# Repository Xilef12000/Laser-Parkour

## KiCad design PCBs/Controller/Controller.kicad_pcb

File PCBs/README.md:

# Library sources:
## RPi Pico
from [github.com/ncarandini/KiCad-RP-Pico](https://github.com/ncarandini/KiCad-RP-Pico):
- `MCU_RaspberryPi_and_Boards.kicad_sym`
- `Pico.wrl`
- `RPi_Pico_SMD_TH.kicad_mod` 

## Würth Elektronik
converted from files provided by [Würth Elektronik](https://www.we-online.com/):
- `WR-DC DC Power Jack Right Angled (6.4).kicad_mod`
- `WR-MJ Modular Jack Horizontal Shielded w. EMI Panel Finger 8P8C Tab Up.kicad_mod`
- `WS-ENTV_4820XX514001.kicad_mod`

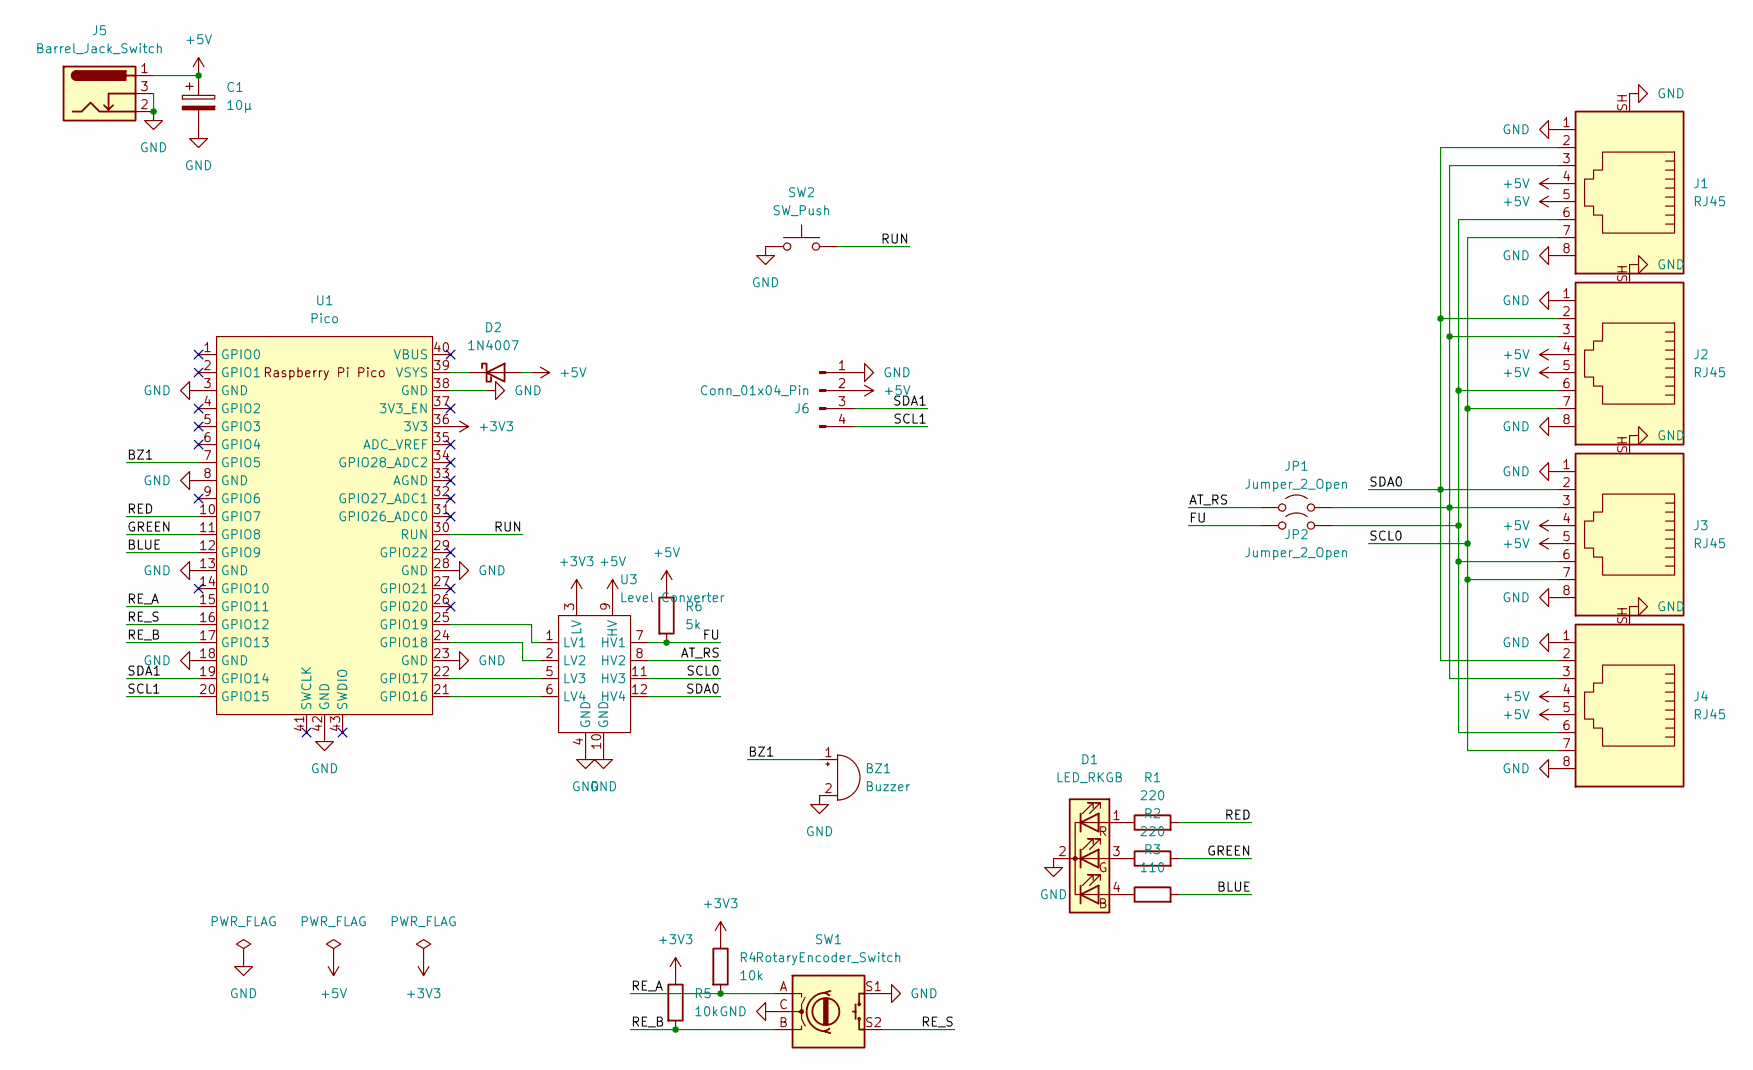
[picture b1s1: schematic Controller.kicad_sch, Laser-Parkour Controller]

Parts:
BZ1: Buzzer; Buzzer_12x9.5RM7.6
C1: 10μ; CP_Radial_D5.0mm_P2.00mm
D1: LED_RKGB; LED_D5.0mm-4_RGB_Wide_Pins
D2: 1N4007; D_DO-41_SOD81_P7.62mm_Horizontal
J1, J2, J3, J4: RJ45; WR-MJ Modular Jack Horizontal Shielded w. EMI Panel Finger 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
J5: Barrel_Jack_Switch; WR-DC DC Power Jack Right Angled (6.4)
J6: Conn_01x04_Pin; PinHeader_1x04_P2.54mm_Vertical
JP1, JP2: Jumper_2_Open; SolderJumper-2_P1.3mm_Open_RoundedPad1.0x1.5mm
R1, R2: 220; R_Axial_DIN0207_L6.3mm_D2.5mm_P10.16mm_Horizontal
R3: 110; R_Axial_DIN0207_L6.3mm_D2.5mm_P10.16mm_Horizontal
R4, R5: 10k; R_Axial_DIN0207_L6.3mm_D2.5mm_P10.16mm_Horizontal
R6: 5k; R_Axial_DIN0207_L6.3mm_D2.5mm_P10.16mm_Horizontal
SW1: RotaryEncoder_Switch; WS-ENTV_4820XX514001
SW2: SW_Push; SW_PUSH_6mm_H4.3mm
U1: Pico; RPi_Pico_SMD_TH
U3: Level Converter; Level_Converter

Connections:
+3V3: R4.1, R5.1, U1.36 (3V3), U3.3 (LV)
+5V: C1.1, D2.2 (A), J1.4, J1.5, J2.4, J2.5, J3.4, J3.5, J4.4, J4.5, J5.1, J6.2, R6.1, U3.9 (HV)
/AT_RS: JP1.1 (A), U3.8 (HV2)
/BLUE: R3.2, U1.12 (GPIO9)
/BZ1: BZ1.1 (+), U1.7 (GPIO5)
/FU: JP2.1 (A), R6.2, U3.7 (HV1)
/GREEN: R2.2, U1.11 (GPIO8)
/RED: R1.2, U1.10 (GPIO7)
/RE_A: R4.2, SW1.A, U1.15 (GPIO11)
/RE_B: R5.2, SW1.B, U1.17 (GPIO13)
/RE_S: SW1.S2, U1.16 (GPIO12)
/RUN: SW2.2, U1.30 (RUN)
/SCL0: J1.7, J2.7, J3.7, J4.7, U3.11 (HV3)
/SCL1: J6.4, U1.20 (GPIO15)
/SDA0: J1.2, J2.2, J3.2, J4.2, U3.12 (HV4)
/SDA1: J6.3, U1.19 (GPIO14)
GND: BZ1.2 (-), C1.2, D1.2 (K), J1.1, J1.8, J1.SH, J2.1, J2.8, J2.SH, J3.1, J3.8, J3.SH, J4.1, J4.8, J4.SH, J5.2, J5.3, J6.1, SW1.C, SW1.S1, SW2.1, U1.3 (GND), U1.8 (GND), U1.13 (GND), U1.18 (GND), U1.23 (GND), U1.28 (GND), U1.38 (GND), U1.42 (GND), U3.4 (GND), U3.10 (GND)
unnamed: D1.4 (BA), R3.1
unnamed: D1.3 (GA), R2.1
unnamed: D1.1 (RA), R1.1
unnamed: D2.1 (K), U1.39 (VSYS)
unnamed: J1.3, J2.3, J3.3, J4.3, JP1.2 (B)
unnamed: J1.6, J2.6, J3.6, J4.6, JP2.2 (B)
unnamed: U1.21 (GPIO16), U3.6 (LV4)
unnamed: U1.22 (GPIO17), U3.5 (LV3)
unnamed: U1.24 (GPIO18), U3.2 (LV2)
unnamed: U1.25 (GPIO19), U3.1 (LV1)

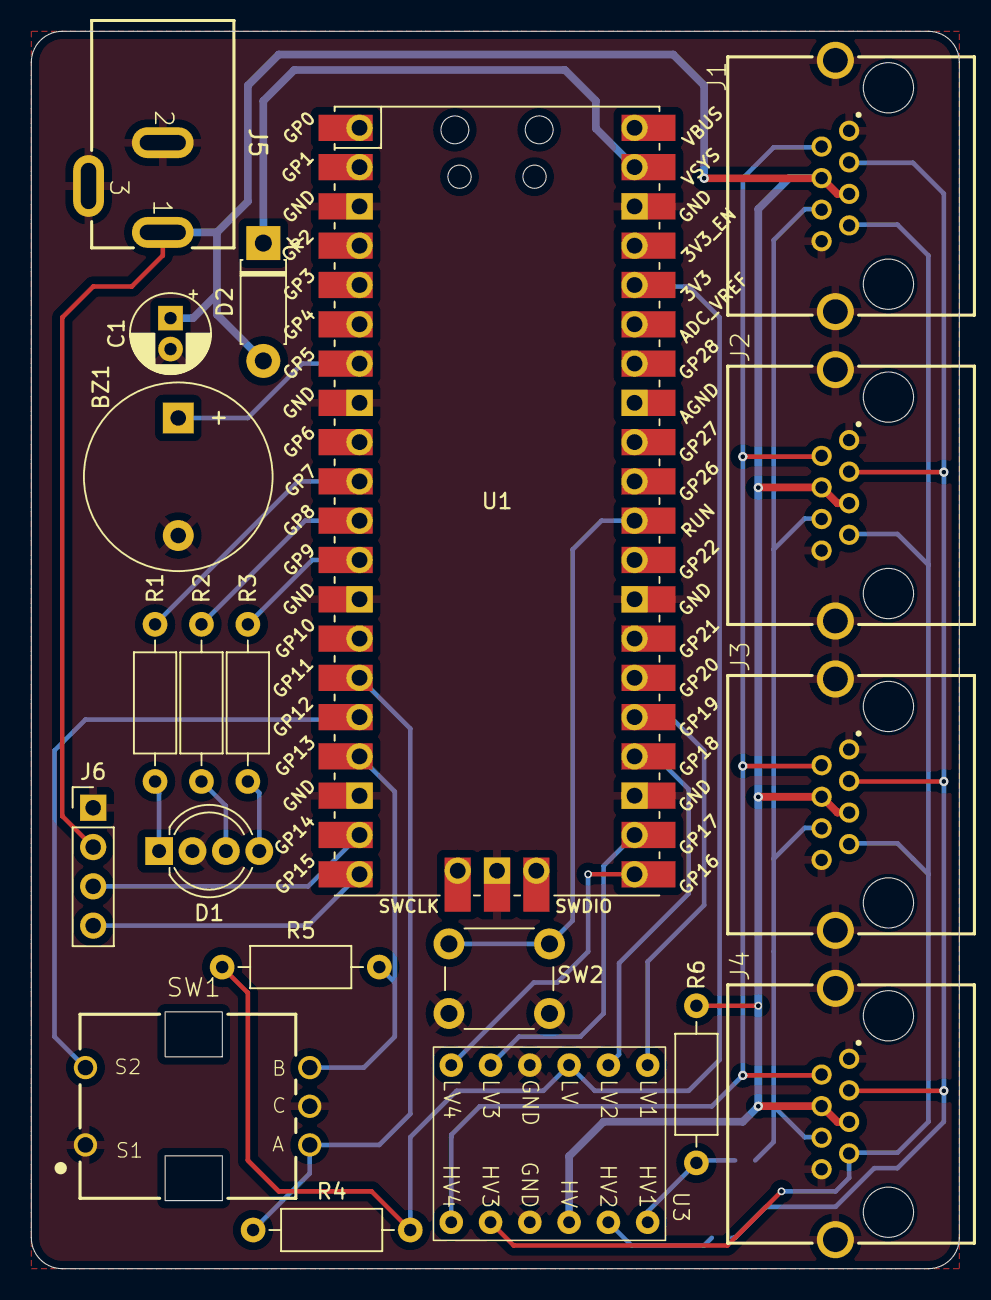
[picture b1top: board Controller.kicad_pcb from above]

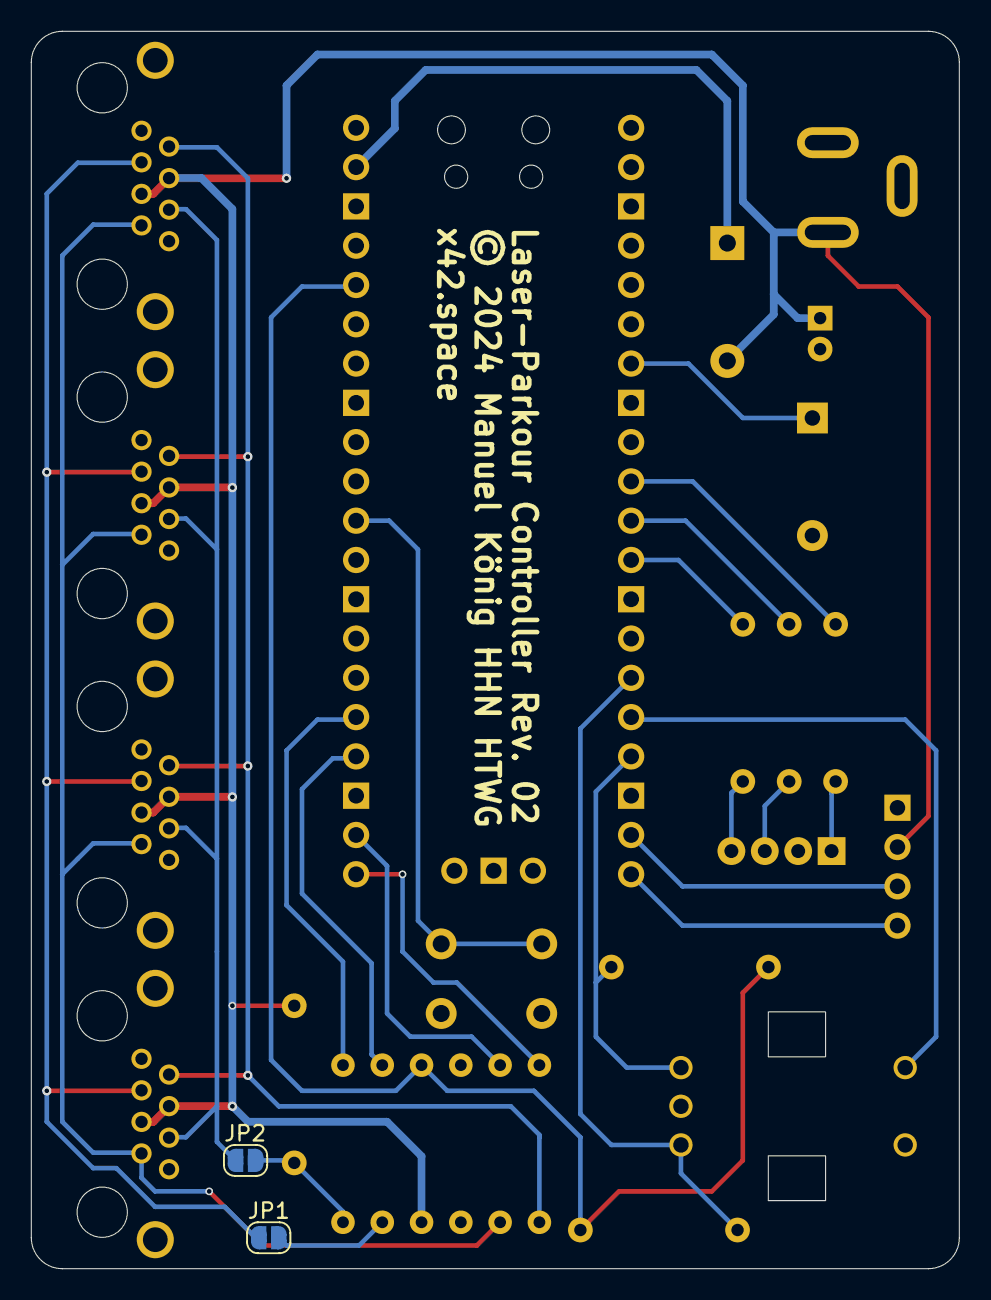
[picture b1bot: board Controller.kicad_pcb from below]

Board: 2 copper layers, 60.0 x 80.0 mm, 22 parts (2 on the bottom side), 27 nets.

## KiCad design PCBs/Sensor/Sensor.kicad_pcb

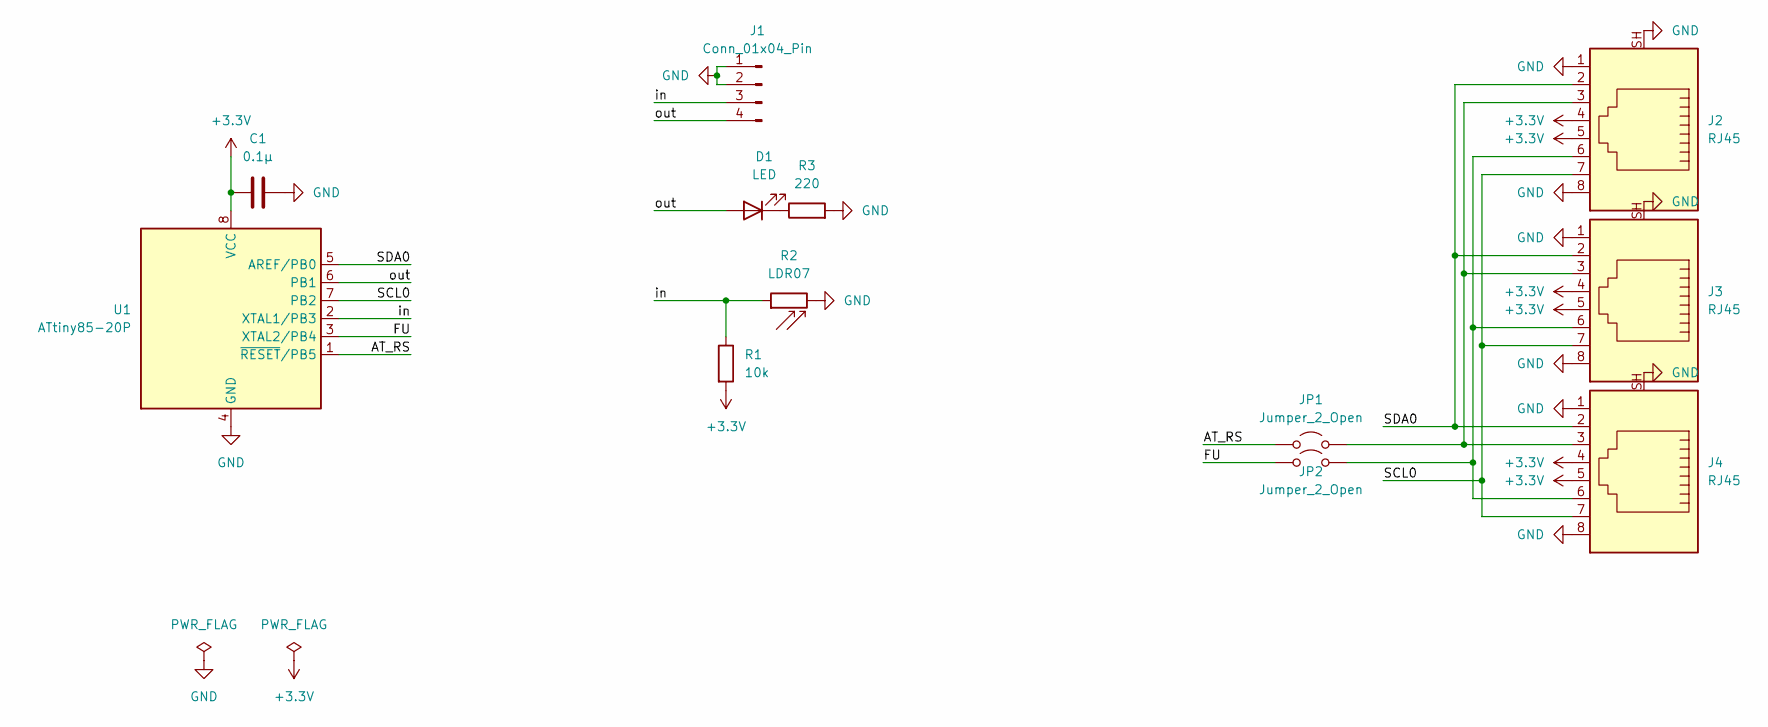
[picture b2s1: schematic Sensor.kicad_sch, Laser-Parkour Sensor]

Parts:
C1: 0.1μ; C_Disc_D3.0mm_W1.6mm_P2.50mm
D1: LED; LED_D5.0mm
J1: Conn_01x04_Pin; PinHeader_1x04_P2.54mm_Vertical
J2, J3, J4: RJ45; WR-MJ Modular Jack Horizontal Shielded w. EMI Panel Finger 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
JP1, JP2: Jumper_2_Open; SolderJumper-2_P1.3mm_Open_RoundedPad1.0x1.5mm
R1: 10k; R_Axial_DIN0207_L6.3mm_D2.5mm_P10.16mm_Horizontal
R2: LDR07; R_LDR_5.1x4.3mm_P3.4mm_Vertical
R3: 220; R_Axial_DIN0207_L6.3mm_D2.5mm_P10.16mm_Horizontal
U1: ATtiny85-20P; DIP-8_W7.62mm

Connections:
+3.3V: C1.1, J2.4, J2.5, J3.4, J3.5, J4.4, J4.5, R1.2, U1.8 (VCC)
/AT_RS: JP1.1 (A), U1.1 (~RESET/PB5)
/FU: JP2.1 (A), U1.3 (XTAL2/PB4)
/SCL0: J2.7, J3.7, J4.7, U1.7 (PB2)
/SDA0: J2.2, J3.2, J4.2, U1.5 (AREF/PB0)
/in: J1.3, R1.1, R2.1, U1.2 (XTAL1/PB3)
/out: D1.2 (A), J1.4, U1.6 (PB1)
GND: C1.2, J1.1, J1.2, J2.1, J2.8, J2.SH, J3.1, J3.8, J3.SH, J4.1, J4.8, J4.SH, R2.2, R3.2, U1.4 (GND)
unnamed: D1.1 (K), R3.1
unnamed: J2.3, J3.3, J4.3, JP1.2 (B)
unnamed: J2.6, J3.6, J4.6, JP2.2 (B)

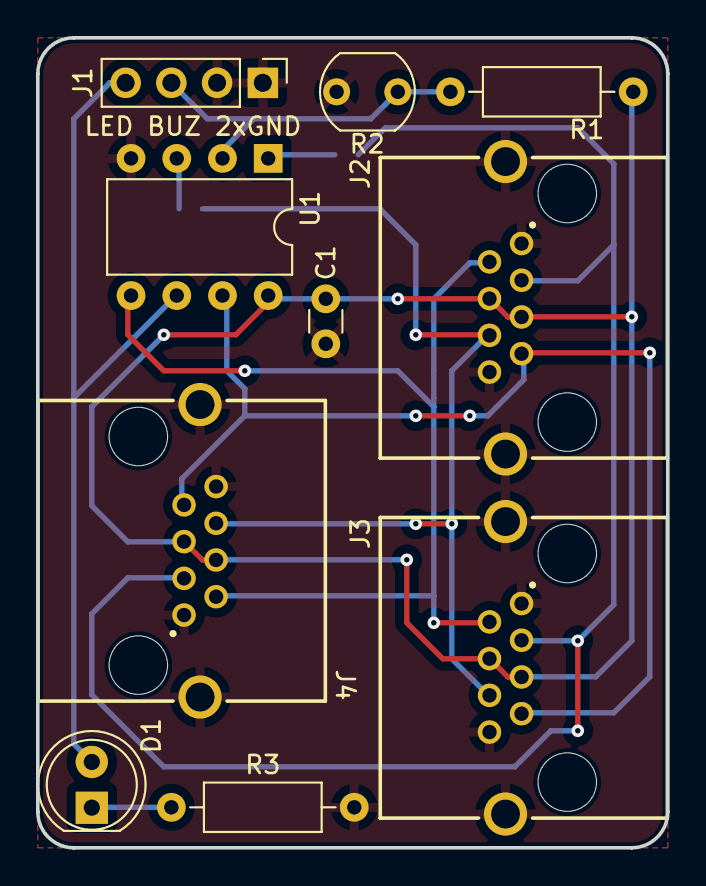
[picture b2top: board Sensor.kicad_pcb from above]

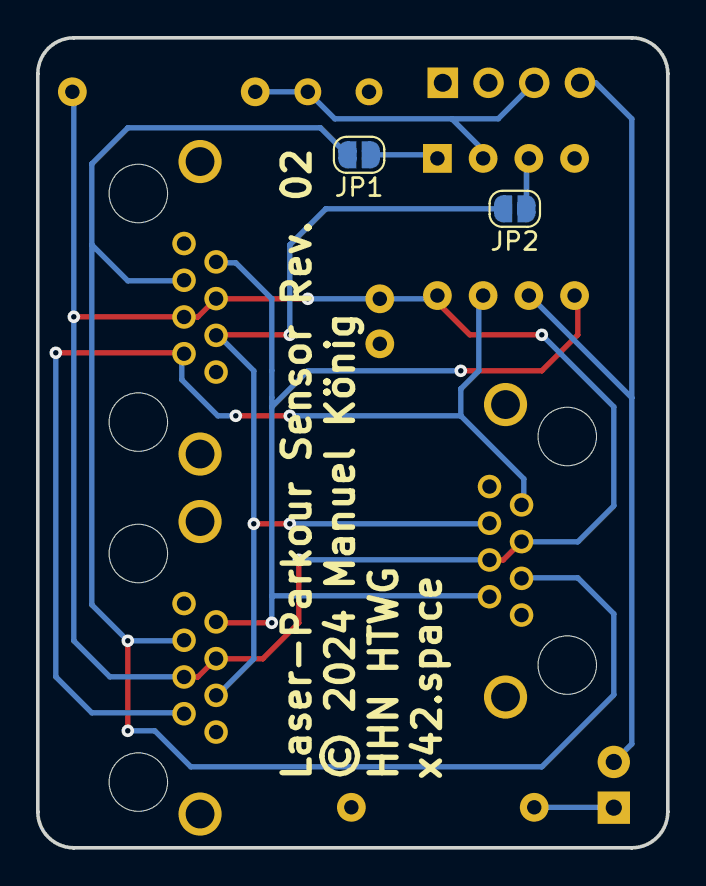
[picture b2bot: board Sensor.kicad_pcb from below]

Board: 2 copper layers, 35.0 x 45.0 mm, 12 parts (2 on the bottom side), 11 nets.

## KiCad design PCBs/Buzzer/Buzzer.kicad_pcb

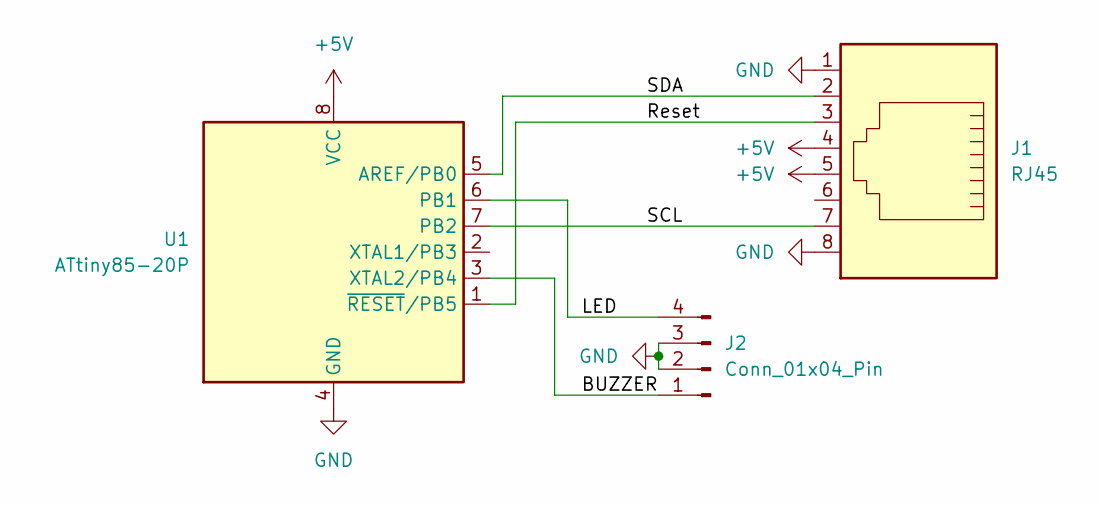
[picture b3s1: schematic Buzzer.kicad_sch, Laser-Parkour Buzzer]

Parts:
J1: RJ45; WR-MJ Modular Jack Horizontal Shielded w. EMI Panel Finger 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
J2: Conn_01x04_Pin; PinHeader_1x04_P2.54mm_Vertical
U1: ATtiny85-20P; DIP-8_W7.62mm

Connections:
+5V: J1.4, J1.5, U1.8 (VCC)
/BUZZER: J2.1, U1.3 (XTAL2/PB4)
/LED: J2.4, U1.6 (PB1)
/Reset: J1.3, U1.1 (~RESET/PB5)
/SCL: J1.7, U1.7 (PB2)
/SDA: J1.2, U1.5 (AREF/PB0)
GND: J1.1, J1.8, J1.S1, J1.S2, J2.2, J2.3, U1.4 (GND)

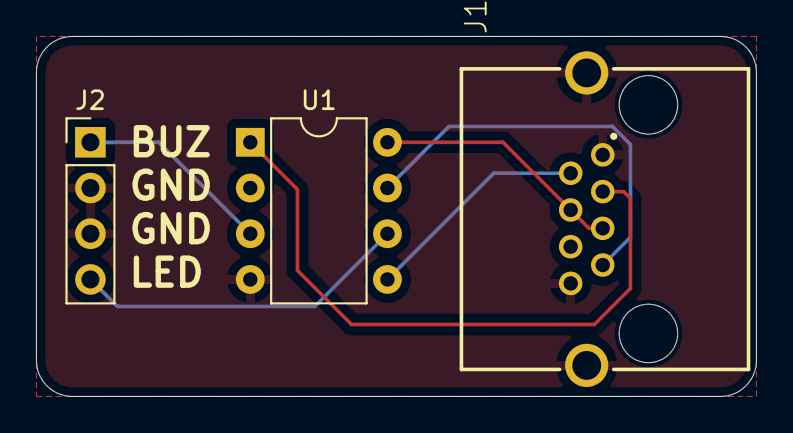
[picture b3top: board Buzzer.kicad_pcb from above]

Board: 2 copper layers, 40.0 x 20.0 mm, 3 parts (0 on the bottom side), 7 nets.

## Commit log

2021-06-18 current laser parcour program
2021-06-18 README
2021-06-18 test sketch
2021-06-18 delet old Readme
2021-06-18 new README.md
2021-06-18 extended wiring diagram
2021-06-18 update wiring diagram
2021-06-18 update dev
2021-06-19 update wiring diagram
    update wiring diagram and rename from "extended wiring diagram" to "wiring diagram 3.0"
2021-06-20 updaate
2021-06-20 add laserdiods
2021-06-20 add laser diode
2021-06-20 now with custom laser-diods
2021-07-23 update wiring diagramm
2021-08-01 corrections for release
2021-08-01 changes for release
2021-08-01 added programs
2021-08-08 correcting "parcour" to "parkour"
2021-08-08 new version 2.1.2
2021-08-08 correcting more spelling mistakes
2021-08-08 corrected spelling mistakes
2021-08-08 changed "laserlab" to "laser-parkour"
2021-08-08 changes.
2021-08-08 deleted arduino stuff
2021-08-08 changed version in comment
2021-08-08 changes for parallel photo-diodes
2021-08-11 deleted unnecessary notes
2021-08-11 deleting old .h-files
2021-08-11 class stuff
2021-08-11 fixing a few things for release
2021-08-11 fixing
2021-08-11 also fixing
2021-08-11 deleted laser-diode image stuff
2021-10-04 added useful stuff
2021-10-05 complete new script
2021-10-05 new wiring diagram
2021-10-11 added a class and functions
2021-10-12 new complicated stuff
2021-10-22 webinterface
2021-10-22 added the testsketch
2021-10-22 name input
2021-10-24 renamed sketch to sketch_esp
2021-10-24 added vs code stuff
2021-10-24 more vs-code stuff
2021-10-24 worked with %appdata%
2021-10-25 web interface working
2021-10-25 removed Serial.println
2021-10-25 new stuff
2021-10-26 working on web-interface
2021-10-28 bug fix
    Fixed the bug, that the sketch loops when laser gets interrupted, and in this time doesn't recognise, when the finish-button gets pressed
2021-10-28 updated the README and added the README.html file
2021-10-28 updated the README
2021-10-28 working web-interface
2021-10-28 better i-frame
2021-10-31 preparing for sd-card
2021-11-01 moved webpage, .htm instead of .html
2021-11-01 new wiring diagramm
2021-11-01 web-page changes
2021-11-01 read from sd-card
2021-11-01 corrected the web-interface
2021-11-01 updated the wiring diagramm
2021-11-01 renamed table files
2021-11-01 .htmll to .htm
2021-11-01 VS-Code stuff
2021-11-26 added 3D-files
2021-11-29 renamed 3d-file folder
2022-01-17 added the Batteriehalter 3d-files
2022-04-01 Laserstrahlung image as svg
2022-04-07 transparent background
2022-04-07 added Laser-Symbol
    original source: https://upload.wikimedia.org/wikipedia/commons/archive/9/94/20080912112604%21Laser-symbol.svg
2022-04-08 new photos
2024-08-18 simple I2C communication
2024-08-18 Sensor PCB schematic
2024-08-24 assigned footprints
2024-08-24 routing
2024-08-24 added info text
2024-08-24 Buzzer
2024-08-24 update footprint
2024-08-24 added nc
2024-08-25 added library content
2024-08-25 controller
2024-08-25 pcb page setup
2024-09-01 update RJ45 pins and pwr_flag
2024-09-01 integrate buzzer PCB into Sensor
2024-09-06 added jumper pad
2024-09-07 update library
2024-09-07 update sensor
2024-09-07 added text
2024-09-08 added Capacitors
2024-09-08 rounded corners
2024-09-08 better rj45 routing
2024-09-08 cleanup
2024-09-23 pi pico w controller
2024-10-06 imported Aisler Board Rules
    https://github.com/AislerHQ/aisler-support
2024-10-06 fixed pcb
2024-10-19 wider traces
2024-10-19 too much changes
2024-11-10 added microdot
    added microdot Version 2.0.6
2024-11-10 using websocket instead of polling
2024-11-10 sensor rescan button
2025-02-22 added Level Converter foodprint
2025-02-22 Controller Rev. 01
2025-02-24 commit to safe current state
2025-02-28 documentation
2025-02-28 update pcb
2025-03-01 statemachine
2025-03-04 handle sensor reconnect
2025-03-04 separate js
    move js to separate file, add css
2025-03-05 laser interrupt penalty
2025-03-05 simple layout
2025-03-16 threshold
2025-03-29 Controller Rev. 02
2025-03-30 changeable threshold
2025-03-30 beep
2025-04-06 lost sensor while running game
2025-04-06 debug leds
2025-04-06 cancel game/setup button
2025-04-06 penalty

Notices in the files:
PCBs/Buzzer/Buzzer.kicad_pcb:
© 2024 Manuel König
PCBs/Controller/Controller.kicad_pcb:
© 2024 Manuel König HHN HTWG
